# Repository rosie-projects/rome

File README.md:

# Projeto ROME (Robótica Móvel nas Escolas)

## Sobre o Projeto
ROME é um projeto educacional dedicado a democratizar o acesso à educação em robótica para escolas públicas e comunidade. O projeto desenvolve ferramentas, materiais didáticos e minicursos de robótica, sendo uma iniciativa de hardware de código aberto que visa transformar alunos de consumidores passivos em desenvolvedores de soluções tecnológicas.

## Objetivos Principais
- Promover inclusão e transformação social através da robótica educacional
- Oferecer recursos flexíveis, de baixo custo e alta escalabilidade
- Estimular a cultura maker e aprendizagem prática
- Desenvolver habilidades como pensamento crítico, criatividade, comunicação e colaboração
- Integrar alunos do ensino médio ao ambiente universitário

## Estrutura do Projeto

```
rome/
├── Artigo/          # Documentação do projeto
├── PCB/         # Arquivos em PDF da esquemática da PCB
├── Plataforma Mecânica/           # Instruções para montagem da estrutura
│   ├── Prática/  # Pratica Docente e arquivos .ino
├── rome-conectado/   # Arquivos em KiCad na PCB

```

## Pré-requisitos

Para executar este projeto, você precisará ter instalado:

- Node.js (versão 14 ou superior)
- npm ou yarn
- Git
- Arduino IDE 1.8.19

## Componentes e Bibliotecas

### Hardware Necessário
- Placa Arduino
- Sensor ultrassônico HC-SR04
- Driver motor TB6612FNG

### Bibliotecas Arduino
1. **SparkFun TB6612FNG**
   - Biblioteca para controle dos motores
   - [Download SparkFun TB6612FNG](https://github.com/sparkfun/SparkFun_TB6612FNG_Arduino_Library)

2. **Ultrasonic**
   - Biblioteca para o sensor ultrassônico
   - [Download Ultrasonic](https://github.com/makerhero/Ultrasonic)

## Instalação

```bash
# Clone o repositório
git clone https://github.com/rosie-projects/rome.git

# Entre no diretório
cd rome

# Instale as dependências
npm install

# Inicie o servidor de desenvolvimento
npm run dev
```

## Como Usar

1. **Montagem do Hardware**
   - Monte a estrutura mecânica seguindo as instruções em `/Plataforma Mecânica`
   - Faça as conexões elétricas conforme o esquemático em `/PCB`
   - Conecte o Arduino, sensor ultrassônico e driver de motor

2. **Configuração do Software**
   - Abra o Arduino IDE 1.8.19
   - Instale as bibliotecas SparkFun TB6612FNG e Ultrasonic
   - Carregue o arquivo `/Prática/Pratica_final.ino`
   - Verifique se as portas definidas no código correspondem às suas conexões

3. **Execução**
   - Após carregar o código, o robô irá:
     - Mover-se para frente automaticamente
     - Detectar obstáculos usando o sensor ultrassônico
     - Desviar quando encontrar obstáculos a menos de 20cm

## Contribuição

1. Faça um Fork do projeto
2. Crie uma branch para sua feature (`git checkout -b feature/AmazingFeature`)
3. Commit suas mudanças (`git commit -m 'Add some AmazingFeature'`)
4. Push para a branch (`git push origin feature/AmazingFeature`)
5. Abra um Pull Request

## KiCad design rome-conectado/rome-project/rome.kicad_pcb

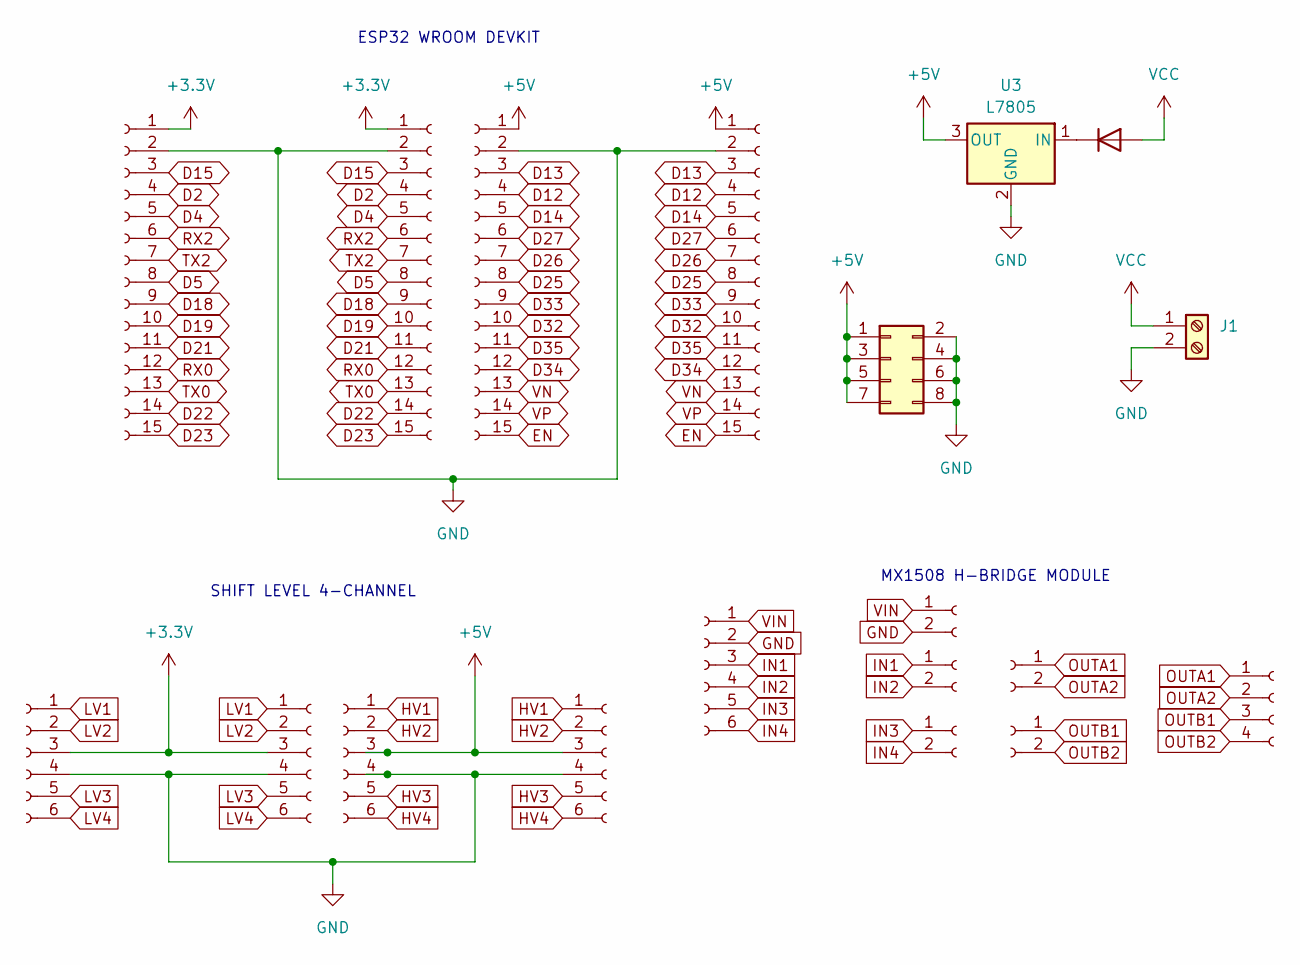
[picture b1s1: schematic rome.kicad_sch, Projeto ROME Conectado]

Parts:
D3: 1N4001; D_DO-41_SOD81_P10.16mm_Horizontal
DEV1: Conn_01x14_Socket; PinSocket_1x15_P2.54mm_Vertical
DEV2: PinSocket_1x15_P2.54mm_Vertical
DEVE1, DEVE2: PinSocket_1x15_P2.54mm_Vertical
HBE1: Conn_01x06_Socket; PinSocket_1x06_P2.54mm_Vertical
HBE2: Conn_01x04_Socket; PinHeader_1x04_P2.54mm_Vertical
HBIN1, HBIN2: Conn_01x02_Socket; PinSocket_1x02_P2.54mm_Vertical
HBOUT1, HBOUT2: Conn_01x02_Socket; PinSocket_1x02_P2.54mm_Vertical
HBP1: Conn_01x02_Socket; PinSocket_1x02_P2.54mm_Vertical
HV1: Conn_01x06_Socket; PinSocket_1x06_P2.54mm_Vertical
HVE1: Conn_01x06_Socket; PinSocket_1x06_P2.54mm_Vertical
J1: Screw_Terminal_01x02; TerminalBlock_bornier-2_P5.08mm
J2: Conn_02x04_Counter_Clockwise; PinHeader_2x04_P2.54mm_Vertical
LV1: Conn_01x06_Socket; PinSocket_1x06_P2.54mm_Vertical
LVE1: Conn_01x06_Socket; PinSocket_1x06_P2.54mm_Vertical
U3: L7805; TO-220-3_Vertical

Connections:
+3.3V: DEV2.1, DEVE2.1, LV1.3, LVE1.3
+5V: DEV1.1, DEVE1.1, HV1.3, HVE1.3, J2.1, J2.3, J2.5, J2.7, U3.3 (OUT)
D2: DEV2.4, DEVE2.4
D4: DEV2.5, DEVE2.5
D5: DEV2.8, DEVE2.8
D12: DEV1.4, DEVE1.4
D13: DEV1.3, DEVE1.3
D14: DEV1.5, DEVE1.5
D15: DEV2.3, DEVE2.3
D18: DEV2.9, DEVE2.9
D19: DEV2.10, DEVE2.10
D21: DEV2.11, DEVE2.11
D22: DEV2.14, DEVE2.14
D23: DEV2.15, DEVE2.15
D25: DEV1.8, DEVE1.8
D26: DEV1.7, DEVE1.7
D27: DEV1.6, DEVE1.6
D32: DEV1.10, DEVE1.10
D33: DEV1.9, DEVE1.9
D34: DEV1.12, DEVE1.12
D35: DEV1.11, DEVE1.11
EN: DEV1.15, DEVE1.15
GND: DEV1.2, DEV2.2, DEVE1.2, DEVE2.2, HBE1.2, HBP1.2, HV1.4, HVE1.4, J1.2, J2.2, J2.4, J2.6, J2.8, LV1.4, LVE1.4, U3.2 (GND)
HV1: HV1.1, HVE1.1
HV2: HV1.2, HVE1.2
HV3: HV1.5, HVE1.5
HV4: HV1.6, HVE1.6
IN1: HBE1.3, HBIN1.1
IN2: HBE1.4, HBIN1.2
IN3: HBE1.5, HBIN2.1
IN4: HBE1.6, HBIN2.2
LV1: LV1.1, LVE1.1
LV2: LV1.2, LVE1.2
LV3: LV1.5, LVE1.5
LV4: LV1.6, LVE1.6
unnamed: D3.1 (K), U3.1 (IN)
OUTA1: HBE2.1, HBOUT1.1
OUTA2: HBE2.2, HBOUT1.2
OUTB1: HBE2.3, HBOUT2.1
OUTB2: HBE2.4, HBOUT2.2
RX0: DEV2.12, DEVE2.12
RX2: DEV2.6, DEVE2.6
TX0: DEV2.13, DEVE2.13
TX2: DEV2.7, DEVE2.7
VCC: D3.2 (A), J1.1
VIN: HBE1.1, HBP1.1
VN: DEV1.13, DEVE1.13
VP: DEV1.14, DEVE1.14

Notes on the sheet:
MX1508 H-BRIDGE MODULE
SHIFT LEVEL 4-CHANNEL
ESP32 WROOM DEVKIT

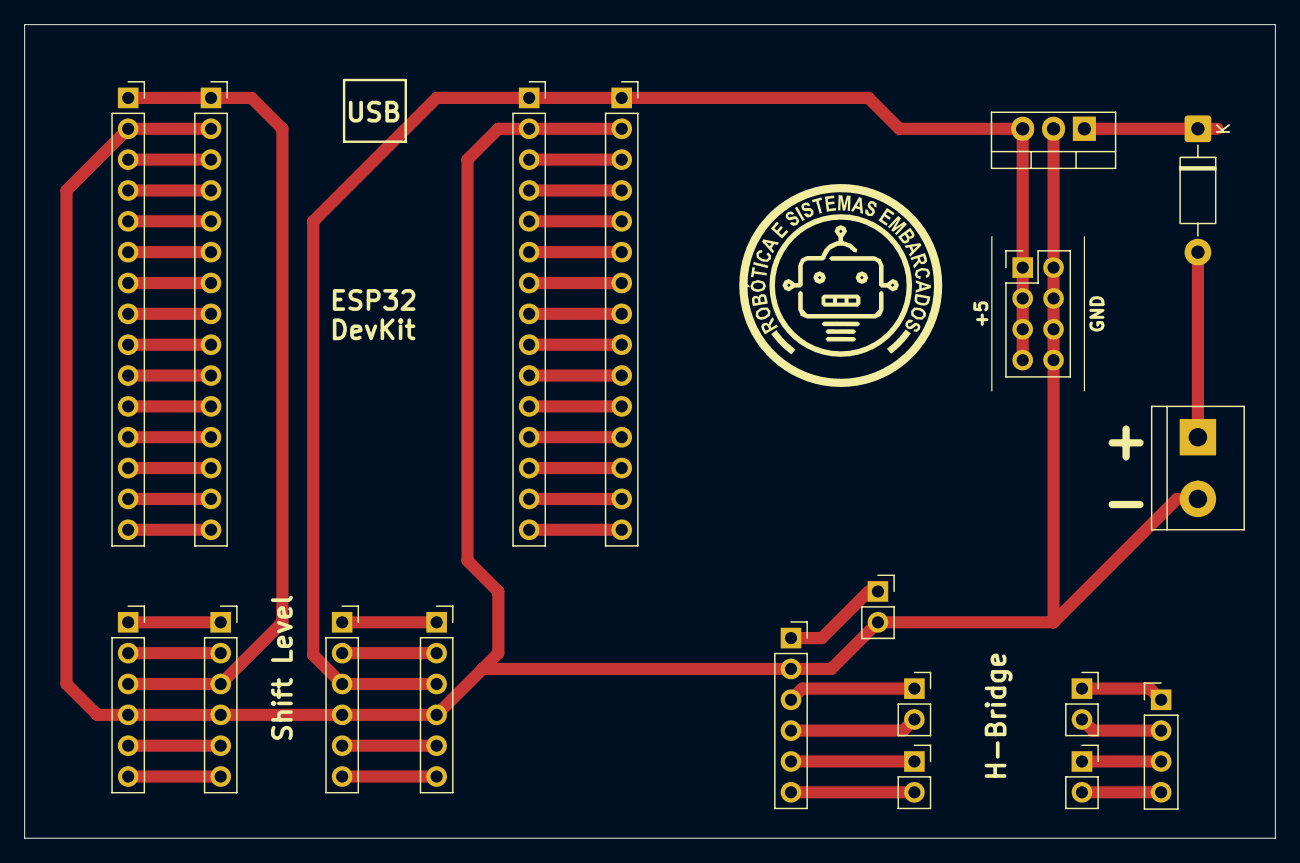
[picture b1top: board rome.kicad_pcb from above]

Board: 2 copper layers, 103.0 x 67.0 mm, 20 parts (0 on the bottom side), 48 nets.

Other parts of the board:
svg2mod: G***; logo_rosie

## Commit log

2022-08-25 Projeto para corta em maquina CNC Router Laser
2022-08-25 Upload Projeto PCB e Artigo COTB
2022-08-25 Imagem da chapa MDF cortada
2022-08-25 Foto base montada
2024-06-06 Rename plataformaA4.jpeg to ROME - MDF CORTADA.jpeg1
2024-06-06 Rename Board1-1.pdf to Esquema da placa.pdf
2024-06-06 Rename BoardEx.pdf to Esquema da placa.pdf
2024-06-06 Rename Schematic.pdf to Esquemática da placa.pdf
2024-06-06 Prática
2025-05-30 Add KiCAD files of Rome Conectado
2025-06-02 Add ROSIE logo at the PCB
2025-06-11 Add gerber files
2025-06-12 Add missing drill files
2025-06-12 Update kicad project
2025-06-20 Update board after position adjustments
2025-08-19 update README & Artigo
2025-12-05 Reorganize papers directory
2025-12-05 Update project and WRE2026 paper
